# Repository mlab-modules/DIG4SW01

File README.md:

# DIG4SW01 - quad-Channel Smart High-Side Switch

Switch for voltage from 3.4 V to 40 V. Resistance in spliced state 160 mOhm. Integrated circuit TPS4H160.

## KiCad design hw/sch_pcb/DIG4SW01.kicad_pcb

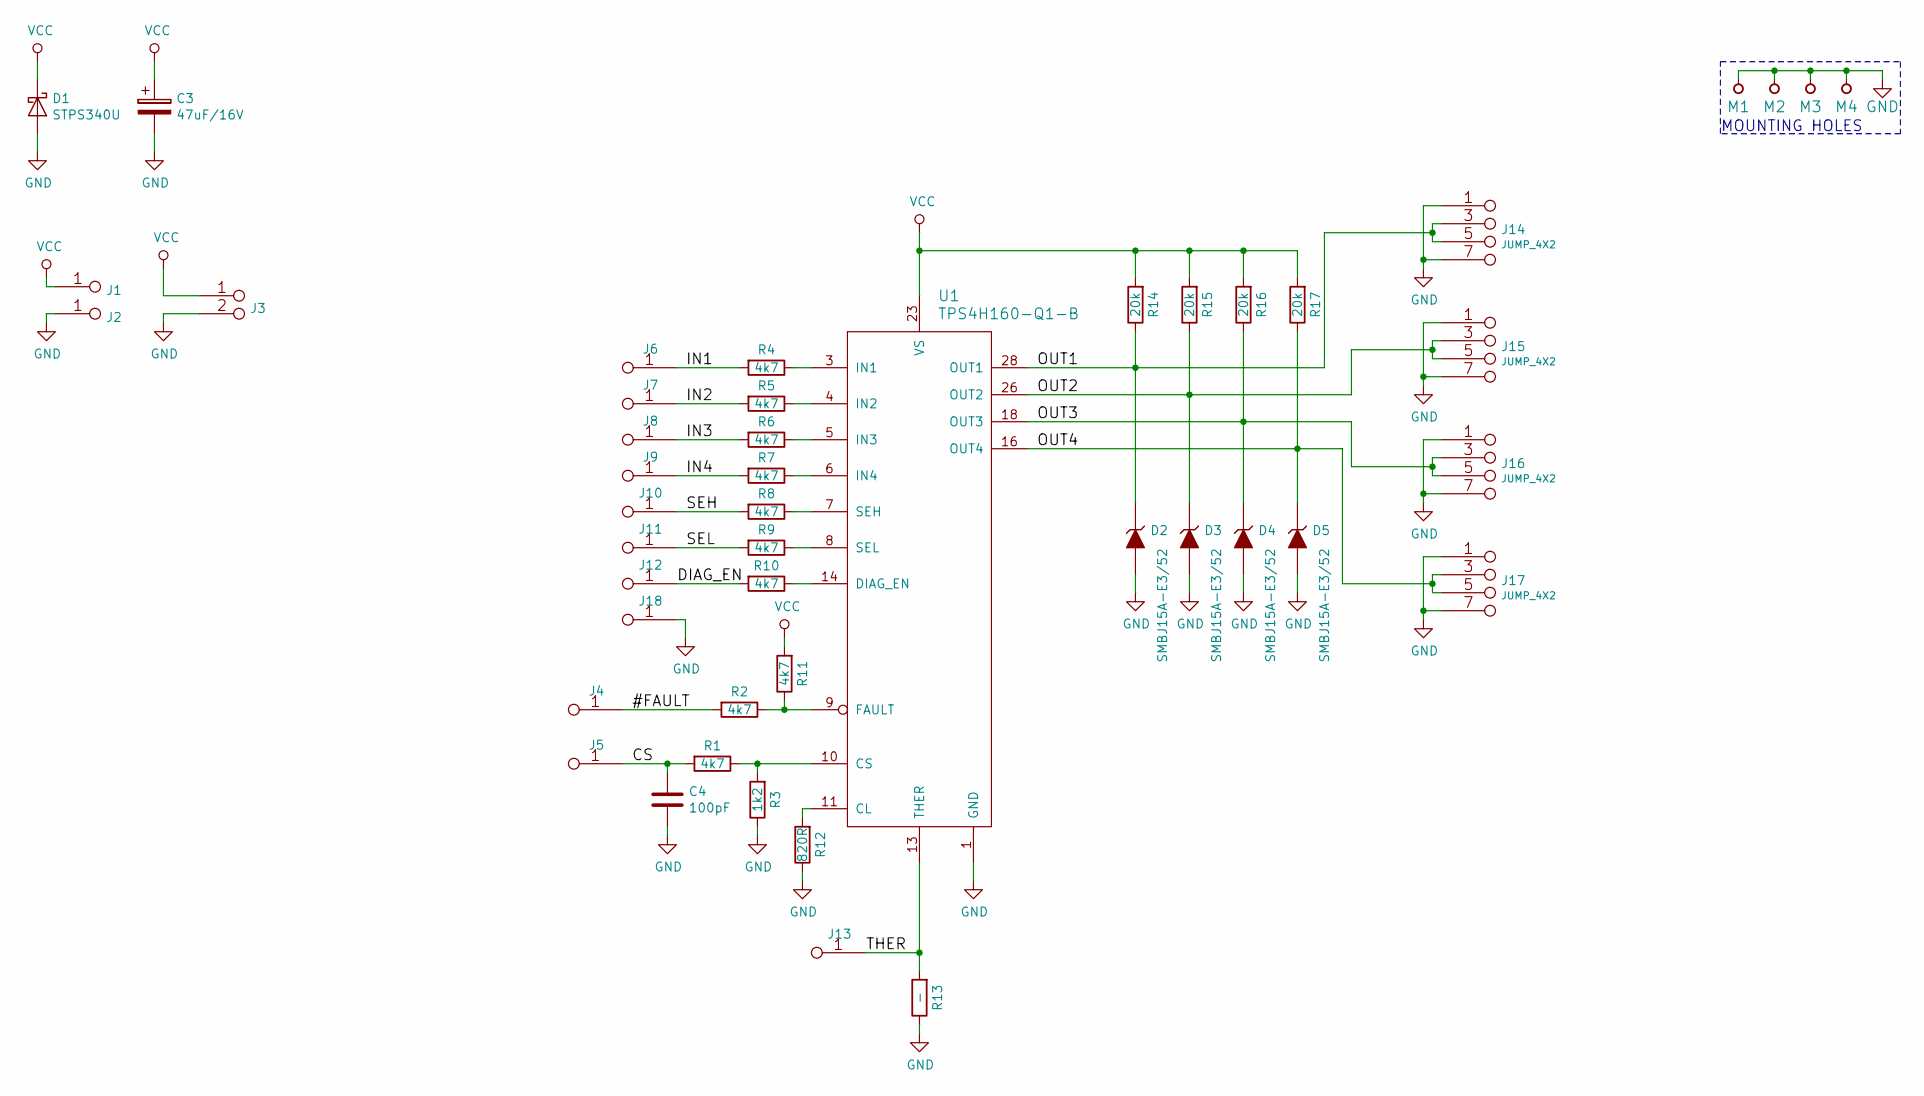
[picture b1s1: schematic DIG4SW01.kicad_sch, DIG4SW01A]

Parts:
C3: 47uF/16V; TantalC_SizeC_Reflow
C4: 100pF; SMD-0805
D1: STPS340U; Diode-SMB_Standard
D2, D3, D4, D5: SMBJ15A-E3/52; SMB_Standard
J1, J2: CONN1_1; WAGO256
J3: CONN1_2; Straight_1x02
J4, J5, J6, J7, J8, J9, J10, J11, J12, J13, J18: JUMP_2x1; Straight_2x01
J14, J15, J16, J17: JUMP_4X2; Straight_2x04
M1, M2, M3, M4: HOLE; MountingHole_3mm
R1, R2, R4, R5, R6, R7, R8, R9, R10, R11: 4k7; SMD-0805
R3: 1k2; SMD-0805
R12: 820R; SMD-0805
R13: -; SMD-0805
R14, R15, R16, R17: 20k; SMD-0805
U1: TPS4H160-Q1-B; HTSSOP28

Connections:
/#FAULT: J4.1, J4.2, R2.2
/CS: C4.1, J5.1, J5.2, R1.2
/DIAG_EN: J12.1, J12.2, R10.2
/IN1: J6.1, J6.2, R4.2
/IN2: J7.1, J7.2, R5.2
/IN3: J8.1, J8.2, R6.2
/IN4: J9.1, J9.2, R7.2
/OUT1: D2.1 (K), J14.3 (4), J14.4, J14.5, J14.6 (5), R14.1, U1.27 (OUT1), U1.28 (OUT1)
/OUT2: D3.1 (K), J15.3 (4), J15.4, J15.5, J15.6 (5), R15.1, U1.25 (OUT2), U1.26 (OUT2)
/OUT3: D4.1 (K), J16.3 (4), J16.4, J16.5, J16.6 (5), R16.1, U1.17 (OUT3), U1.18 (OUT3)
/OUT4: D5.1 (K), J17.3 (4), J17.4, J17.5, J17.6 (5), R17.1, U1.15 (OUT4), U1.16 (OUT4)
/SEH: J10.1, J10.2, R8.2
/SEL: J11.1, J11.2, R9.2
/THER: J13.1, J13.2, R13.2, U1.13 (THER)
GND: C3.2, C4.2, D1.2 (A), D2.2 (A), D3.2 (A), D4.2 (A), D5.2 (A), J2.1, J3.2 (PM), J14.1 (2), J14.2, J14.7 (8), J14.8, J15.1 (2), J15.2, J15.7 (8), J15.8, J16.1 (2), J16.2, J16.7 (8), J16.8, J17.1 (2), J17.2, J17.7 (8), J17.8, J18.1, J18.2, M1.1, M2.1, M3.1, M4.1, R3.1, R12.1, R13.1, U1.1 (GND), U1.12 (GND), U1.29 (GND)
unnamed: R1.1, R3.2, U1.10 (CS)
unnamed: R4.1, U1.3 (IN1)
unnamed: R5.1, U1.4 (IN2)
unnamed: R6.1, U1.5 (IN3)
unnamed: R7.1, U1.6 (IN4)
unnamed: R8.1, U1.7 (SEH)
unnamed: R9.1, U1.8 (SEL)
unnamed: R10.1, U1.14 (DIAG_EN)
unnamed: R2.1, R11.1, U1.9 (FAULT)
unnamed: R12.2, U1.11 (CL)
VCC: C3.1, D1.1 (K), J1.1, J3.1, R11.2, R14.2, R15.2, R16.2, R17.2, U1.20 (VS), U1.21 (VS), U1.22 (VS), U1.23 (VS)

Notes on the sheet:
MOUNTING HOLES

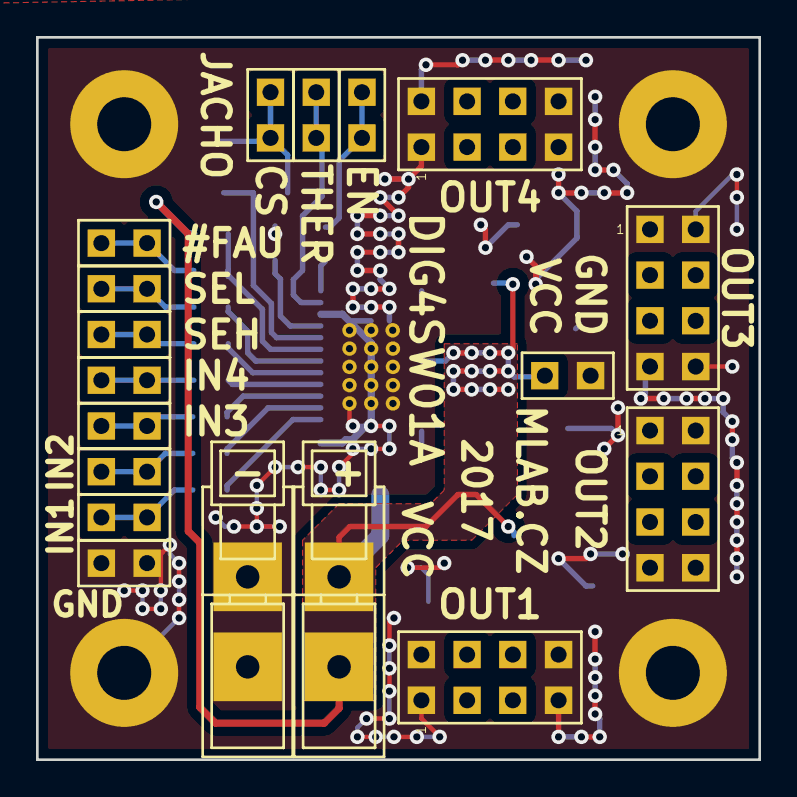
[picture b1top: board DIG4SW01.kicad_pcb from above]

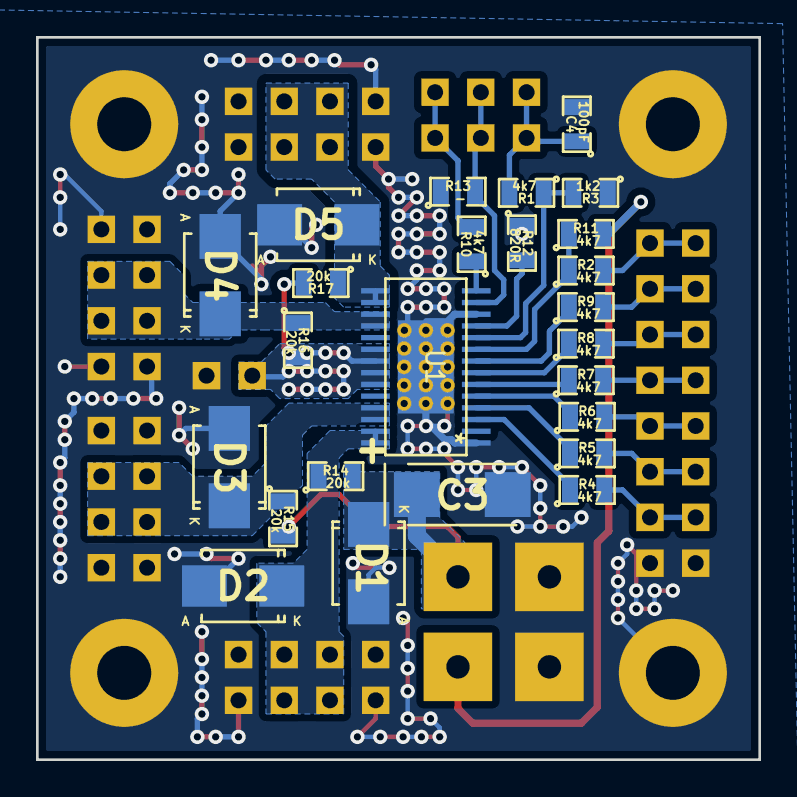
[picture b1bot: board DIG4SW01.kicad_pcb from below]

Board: 2 copper layers, 40.1 x 40.1 mm, 47 parts (25 on the bottom side), 26 nets.

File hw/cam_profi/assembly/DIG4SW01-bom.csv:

Component,Description,Part,References,Value,Footprint,Quantity Per PCB,Datasheet
1,,C,C4,100pF,SMD-0805,1,
2,,CP,C3,47uF/16V,TantalC_SizeC_Reflow,1,
3,,D_ZENER,D2D3D4D5,SMBJ15A-E3/52,SMB_Standard,4,
4,,D_Schottky,D1,STPS340U,Diode-SMB_Standard,1,
5,,CONN1_1,J1J2,CONN1_1,WAGO256,2,
6,,CONN1_2,J3,CONN1_2,Straight_1x02,1,
7,,JUMP_2x1,J4J5J6J7J8J9J10J11J12J13J18,JUMP_2x1,Straight_2x01,11,
8,,JUMP_4X2,J14J15J16J17,JUMP_4X2,Straight_2x04,4,
9,,R,R12,820R,SMD-0805,1,
10,,R,R3,1k2,SMD-0805,1,
11,,R,R1R2R4R5R6R7R8R9R10R11,4k7,SMD-0805,10,
12,,R,R14R15R16R17,20k,SMD-0805,4,
13,,R,R13,-,SMD-0805,1,
14,,TPS4H160-Q1-B,U1,TPS4H160-Q1-B,HTSSOP28,1,

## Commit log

2023-04-01 Adding force option to enable splitting in not fresh copy of Modules repository.
2023-09-17 automated commit; add github actions
2023-09-17 Update workflow files
2023-09-17 Update metadata files
2024-07-06 Update project to KiCADv7.
2024-07-06 Update actions products
2024-07-06 Update documentation.
